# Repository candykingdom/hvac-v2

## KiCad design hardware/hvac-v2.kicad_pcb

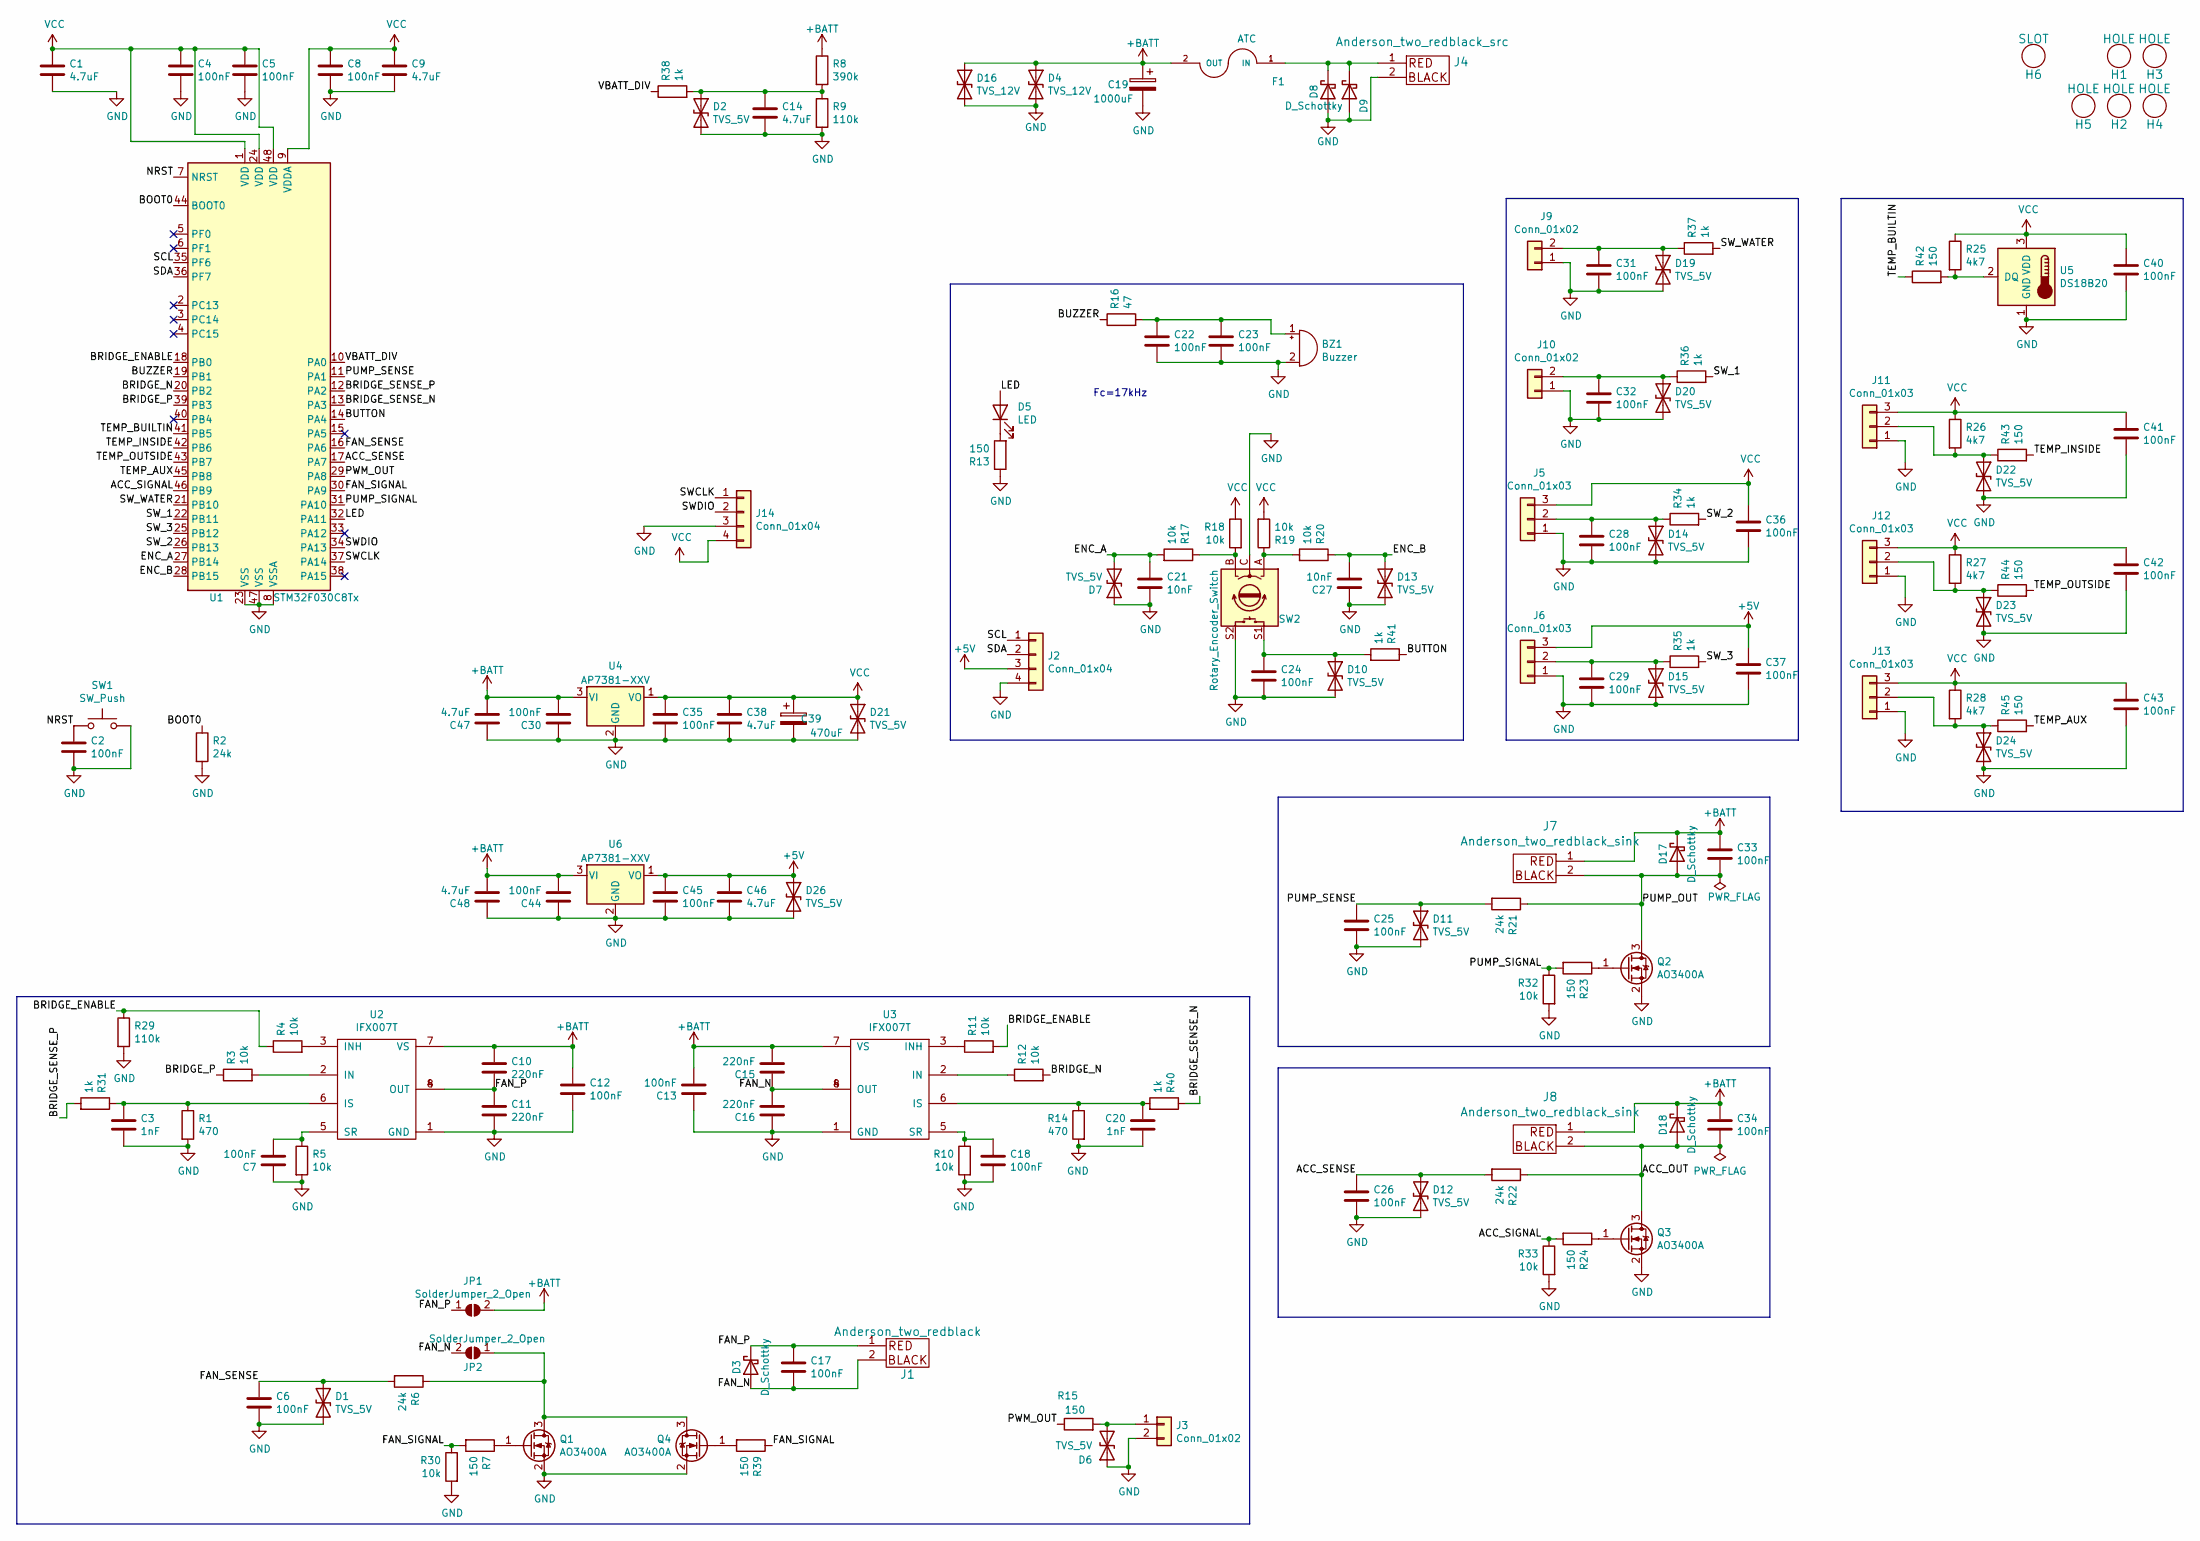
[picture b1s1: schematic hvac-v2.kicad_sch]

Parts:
BZ1: Buzzer; MURATA_PKM13EPYH4000-A0; MPN PKM13EPYH4000-A0
C1, C9, C14, C38, C46, C47, C48: 4.7uF; C_0603_1608Metric; LCSC C19666
C2, C4, C5, C6, C7, C8, C12, C13, C17, C18, C22, C23, C24, C25, C26, C28, C29, C30, C31, C32, C33, C34, C35, C36, C37, C40, C41, C42, C43, C44, C45: 100nF; C_0402_1005Metric; LCSC C307331
C3, C20: 1nF; C_0402_1005Metric; LCSC C1523
C10, C11, C15, C16: 220nF; C_0805_2012Metric; LCSC C5378
C19: 1000uF; CP_Radial_D10.0mm_P5.00mm; MPN 25PK1000MEFC10X16
C21, C27: 10nF; C_0402_1005Metric; LCSC C15195
C39: 470uF; CP_Radial_D10.0mm_P5.00mm; MPN 25PK1000MEFC10X16
D1, D2, D6, D7, D10, D11, D12, D13, D14, D15, D19, D20, D21, D22, D23, D24, D26: TVS_5V; D_SOD-323; LCSC C182013
D3, D8, D9, D17, D18: D_Schottky; D_DO-201AD_P12.70mm_Horizontal; MPN SB10150TA
D4, D16: TVS_12V; D_SMB_Handsoldering; MPN SMBJ16CA
D5: LED; LED_0805_2012Metric; LCSC C84256
F1: ATC; FUSE_3550-2; MPN 3550-2
H1, H2, H3, H4, H5: HOLE; HOLE_M4
H6: SLOT; SLOT_W2mm_H8mm
J1: Anderson_two_redblack; Anderson_1336G1_right_angle_bottom_two
J2, J14: Conn_01x04; PinHeader_1x04_P2.54mm_Horizontal
J3, J9, J10: Conn_01x02; PinHeader_1x02_P2.54mm_Horizontal
J4: Anderson_two_redblack_src; Anderson_1336G1_right_angle_bottom_two
J5, J6, J11, J12, J13: Conn_01x03; PinHeader_1x03_P2.54mm_Horizontal
J7, J8: Anderson_two_redblack_sink; Anderson_1336G1_right_angle_bottom_two
JP1, JP2: SolderJumper_2_Open; SolderJumper-2_P1.3mm_Open_TrianglePad1.0x1.5mm
Q1, Q2, Q3, Q4: AO3400A; SOT-23; LCSC C20917
R1, R14: 470; R_0603_1608Metric; LCSC C23179
R2, R6, R21, R22: 24k; R_0603_1608Metric; LCSC C23352
R3, R4, R5, R10, R11, R12, R17, R18, R19, R20, R30, R32, R33: 10k; R_0603_1608Metric; LCSC C25804
R7, R13, R15, R23, R24, R39, R42, R43, R44, R45: 150; R_0603_1608Metric; LCSC C22808
R8: 390k; R_0603_1608Metric; LCSC C23150
R9, R29: 110k; R_0603_1608Metric; LCSC C25805
R16: 47; R_0603_1608Metric; LCSC C23182
R25, R26, R27, R28: 4k7; R_0603_1608Metric; LCSC C23162
R31, R40, R41: 1k; R_0603_1608Metric; LCSC C11702
R34, R35, R36, R37, R38: 1k; R_0603_1608Metric; LCSC C22808
SW1: SW_Push; SW_TACTILE_5.1MM_TS-1187A-C-D-B; LCSC C318884
SW2: Rotary_Encoder_Switch; BOURNS_PEC12R-4xxxF-Sxxxx; MPN PEC12R-4230F-S0024
U1: STM32F030C8Tx; LQFP-48_7x7mm_P0.5mm; LCSC C23922
U2, U3: IFX007T; TO-263-7_TabPin8; MPN IFX007T
U4: AP7381-XXV; TO-92L_Inline_Wide; MPN AP7381-33V
U5: DS18B20; TO-92_Inline; MPN DS18B20
U6: AP7381-XXV; TO-92L_Inline_Wide; MPN AP7381-50V

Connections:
+5V: C37.1, C45.1, C46.1, D26.1 (A1), J2.3, J6.3, U6.1 (VO)
+BATT: C10.1, C12.1, C13.2, C15.2, C19.1, C30.2, C33.1, C34.1, C44.2, C47.2, C48.2, D4.1 (A1), D16.1 (A1), D17.1 (K), D18.1 (K), F1.2 (OUT), J7.1, J8.1, JP1.2 (B), R8.1, U2.7 (VS), U3.7 (VS), U4.3 (VI), U6.3 (VI)
/ACC_OUT: C34.2, D18.2 (A), J8.2, Q3.3 (D), R22.1
/ACC_SENSE: C26.1, D12.1 (A1), R22.2, U1.17 (PA7)
/ACC_SIGNAL: R24.2, R33.1, U1.46 (PB9)
/BOOT0: R2.1, U1.44 (BOOT0)
/BRIDGE_ENABLE: R4.1, R11.2, R29.1, U1.18 (PB0)
/BRIDGE_N: R12.2, U1.20 (PB2)
/BRIDGE_P: R3.1, U1.39 (PB3)
/BRIDGE_SENSE_N: R40.1, U1.13 (PA3)
/BRIDGE_SENSE_P: R31.2, U1.12 (PA2)
/BUTTON: R41.1, U1.14 (PA4)
/BUZZER: R16.1, U1.19 (PB1)
/ENC_A: C21.1, D7.2 (A2), R17.2, U1.27 (PB14)
/ENC_B: C27.2, D13.1 (A1), R20.1, U1.28 (PB15)
/FAN_N: C15.1, C16.2, C17.2, D3.2 (A), J1.2, JP2.2 (B), U3.4 (OUT), U3.8 (OUT)
/FAN_P: C10.2, C11.1, C17.1, D3.1 (K), J1.1, JP1.1 (A), U2.4 (OUT), U2.8 (OUT)
/FAN_SENSE: C6.1, D1.1 (A1), R6.2, U1.16 (PA6)
/FAN_SIGNAL: R7.2, R30.1, R39.1, U1.30 (PA9)
/LED: D5.2 (A), U1.32 (PA11)
/NRST: C2.1, SW1.1, U1.7 (NRST)
/PUMP_OUT: C33.2, D17.2 (A), J7.2, Q2.3 (D), R21.1
/PUMP_SENSE: C25.1, D11.1 (A1), R21.2, U1.11 (PA1)
/PUMP_SIGNAL: R23.2, R32.1, U1.31 (PA10)
/PWM_OUT: R15.1, U1.29 (PA8)
/SCL: J2.1, U1.35 (PF6)
/SDA: J2.2, U1.36 (PF7)
/SWCLK: J14.1, U1.37 (PA14)
/SWDIO: J14.2, U1.34 (PA13)
/SW_1: R36.2, U1.22 (PB11)
/SW_2: R34.2, U1.26 (PB13)
/SW_3: R35.2, U1.25 (PB12)
/SW_WATER: R37.2, U1.21 (PB10)
/TEMP_AUX: R45.2, U1.45 (PB8)
/TEMP_BUILTIN: R42.1, U1.41 (PB5)
/TEMP_INSIDE: R43.2, U1.42 (PB6)
/TEMP_OUTSIDE: R44.2, U1.43 (PB7)
/VBATT_DIV: R38.1, U1.10 (PA0)
GND: BZ1.2 (+), C1.2, C2.2, C3.2, C4.2, C5.2, C6.2, C7.1, C8.2, C9.2, C11.2, C12.2, C13.1, C14.2, C16.1, C18.2, C19.2, C20.2, C21.2, C22.2, C23.2, C24.2, C25.2, C26.2, C27.1, C28.2, C29.2, C30.1, C31.2, C32.2, C35.2, C36.2, C37.2, C38.2, C39.2, C40.2, C41.2, C42.2, C43.2, C44.1, C45.2, C46.2, C47.1, C48.1, D1.2 (A2), D2.2 (A2), D4.2 (A2), D6.1 (A1), D7.1 (A1), D8.2 (A), D9.2 (A), D10.2 (A2), D11.2 (A2), D12.2 (A2), D13.2 (A2), D14.2 (A2), D15.2 (A2), D16.2 (A2), D19.2 (A2), D20.2 (A2), D21.2 (A2), D22.2 (A2), D23.2 (A2), D24.2 (A2), D26.2 (A2), J2.4, J3.2, J4.2, J5.1, J6.1, J9.1, J10.1, J11.1, J12.1, J13.1, J14.3, Q1.2 (S), Q2.2 (S), Q3.2 (S), Q4.2 (S), R1.2, R2.2, R5.2, R9.2, R10.2, R13.1, R14.2, R29.2, R30.2, R32.2, R33.2, SW1.2, SW2.C, SW2.S2, U1.8 (VSSA), U1.23 (VSS), U1.47 (VSS), U2.1 (GND), U3.1 (GND), U4.2 (GND), U5.1 (GND), U6.2 (GND)
unnamed: BZ1.1 (-), C22.1, C23.1, R16.2
unnamed: C3.1, R1.1, R31.1, U2.6 (IS)
unnamed: C7.2, R5.1, U2.5 (SR)
unnamed: C14.1, D2.1 (A1), R8.2, R9.1, R38.2
unnamed: C18.1, R10.1, U3.5 (SR)
unnamed: C20.1, R14.1, R40.2, U3.6 (IS)
unnamed: C24.1, D10.1 (A1), R41.2, SW2.S1
unnamed: C28.1, D14.1 (A1), J5.2, R34.1
unnamed: C29.1, D15.1 (A1), J6.2, R35.1
unnamed: C31.1, D19.1 (A1), J9.2, R37.1
unnamed: C32.1, D20.1 (A1), J10.2, R36.1
unnamed: D5.1 (K), R13.2
unnamed: D6.2 (A2), J3.1, R15.2
unnamed: D8.1 (K), D9.1 (K), F1.1 (IN), J4.1
unnamed: D22.1 (A1), J11.2, R26.2, R43.1
unnamed: D23.1 (A1), J12.2, R27.2, R44.1
unnamed: D24.1 (A1), J13.2, R28.2, R45.1
unnamed: JP2.1 (A), Q1.3 (D), Q4.3 (D), R6.1
unnamed: Q1.1 (G), R7.1
unnamed: Q2.1 (G), R23.1
unnamed: Q3.1 (G), R24.1
unnamed: Q4.1 (G), R39.2
unnamed: R3.2, U2.2 (IN)
unnamed: R4.2, U2.3 (INH)
unnamed: R11.1, U3.3 (INH)
unnamed: R12.1, U3.2 (IN)
unnamed: R17.1, R18.2, SW2.B
unnamed: R19.1, R20.2, SW2.A
unnamed: R25.2, R42.2, U5.2 (DQ)
VCC: C1.1, C4.1, C5.1, C8.1, C9.1, C35.1, C36.1, C38.1, C39.1, C40.1, C41.1, C42.1, C43.1, D21.1 (A1), J5.3, J11.3, J12.3, J13.3, J14.4, R18.1, R19.2, R25.1, R26.1, R27.1, R28.1, U1.1 (VDD), U1.9 (VDDA), U1.24 (VDD), U1.48 (VDD), U4.1 (VO), U5.3 (VDD)

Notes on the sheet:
Fc=17kHz

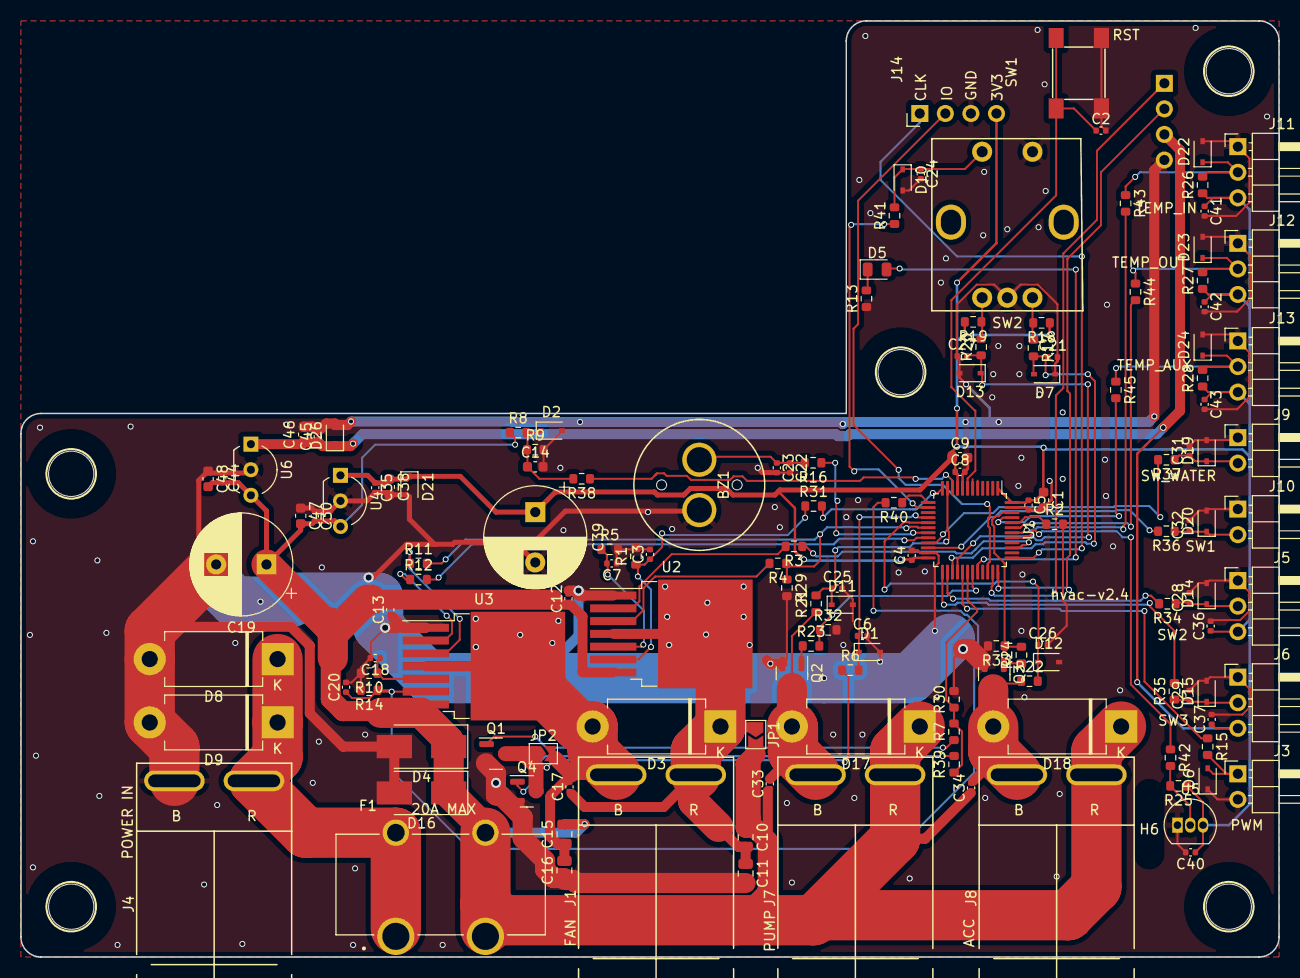
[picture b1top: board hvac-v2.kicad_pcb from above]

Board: 2 copper layers, 125.0 x 93.0 mm, 154 parts (1 on the bottom side), 69 nets.

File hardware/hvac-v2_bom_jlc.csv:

"Comment","Designator","Footprint","LCSC Part #"
"4.7uF","C1,C9,C14,C38,C46,C47,C48","C_0603_1608Metric","C19666"
"100nF","C2,C4,C5,C6,C7,C8,C12,C13,C17,C18,C22,C23,C24,C25,C26,C28,C29,C30,C31,C32,C33,C34,C35,C36,C37,C40,C41,C42,C43,C44,C45","C_0402_1005Metric","C307331"
"1nF","C3,C20","C_0402_1005Metric","C1523"
"220nF","C10,C11,C15,C16","C_0805_2012Metric","C5378"
"10nF","C21,C27","C_0402_1005Metric","C15195"
"TVS_5V","D1,D2,D6,D7,D10,D11,D12,D13,D14,D15,D19,D20,D21,D22,D23,D24,D26","D_SOD-323","C182013"
"LED","D5","LED_0805_2012Metric","C84256"
"AO3400A","Q1,Q2,Q3,Q4","SOT-23","C20917"
"470","R1,R14","R_0603_1608Metric","C23179"
"24k","R2,R6,R21,R22","R_0603_1608Metric","C23352"
"10k","R3,R4,R5,R10,R11,R12,R17,R18,R19,R20,R30,R32,R33","R_0603_1608Metric","C25804"
"150","R7,R13,R15,R23,R24,R39,R42,R43,R44,R45","R_0603_1608Metric","C22808"
"390k","R8","R_0603_1608Metric","C23150"
"110k","R9,R29","R_0603_1608Metric","C25805"
"47","R16","R_0603_1608Metric","C23182"
"4k7","R25,R26,R27,R28","R_0603_1608Metric","C23162"
"1k","R31,R40,R41","R_0603_1608Metric","C11702"
"1k","R34,R35,R36,R37,R38","R_0603_1608Metric","C22808"
"SW_Push","SW1","SW_TACTILE_5.1MM_TS-1187A-C-D-B","C318884"
"STM32F030C8Tx","U1","LQFP-48_7x7mm_P0.5mm","C23922"

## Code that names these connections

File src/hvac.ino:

#include <LiquidCrystal_I2C.h>
#include <STM32TimerInterrupt.h>
#include <STM32_ISR_Timer.h>
#include <Tone.h>
#include <Wire.h>
#include <menu.h>
#include <menuIO/chainStream.h>
#include <menuIO/clickEncoderIn.h>
#include <menuIO/liquidCrystalOutI2C.h>
#include <menuIO/serialIn.h>
#include <menuIO/serialOut.h>
#include <FlashStorage_STM32.h>

#include "arduino-inputs.h"
#include "arduino-outputs.h"
#include "fake-outputs.h"
#include "inputs.h"
#include "outputs.h"
#include "runner.h"

// Pin definitions
constexpr int kBuzzerPin = PB1;
constexpr int kEncAPin = PB14;
constexpr int kEncBPin = PB15;
// TODO: switch to actual encoder button once its connected to the micro
// constexpr int kEncButtonPin = PB11; // v2.3 with hotfix
constexpr int kEncButtonPin = PA4;  // v2.4

constexpr int kFanSensePin = PA6;
constexpr int kPumpSensePin = PA1;
constexpr int kBridgeSenseNPin = PA3;
constexpr int kBridgeSensePPin = PA2;

// Tuning constants
constexpr uint16_t kUpdateTempMs = 1000;
constexpr uint32_t kIdleBacklightOffMs = 30 * 1000;

// State
uint32_t update_display_at = 0;
uint32_t backlight_off_at = 0;

const constexpr int kMaxDepth = 4;

constexpr FanType kFanType = FanType::MOSFET_BANGBANG;
ArduinoInputs inputs;
ArduinoOutputs outputs(kFanType);

RunnerParams runner_params;
Runner runner(runner_params, inputs, outputs);

uint16_t fan_sense = 0;
uint16_t pump_sense = 0;
uint16_t bridge_sense_n = 0;
uint16_t bridge_sense_p = 0;

LiquidCrystal_I2C lcd(/*address=*/0x27, /*columns=*/16, /*rows=*/2);
ClickEncoder clickEncoder(kEncAPin, kEncBPin, kEncButtonPin,
                          /*stepsPerNotch=*/4);
ClickEncoderStream encStream(clickEncoder, 1);

void SaveConfig() {
  EEPROM.put(0, runner_params);
}

// clang-format off
TOGGLE(runner_params.sound_on, sound_on_menu, "Sound:", doNothing, noEvent, wrapStyle
  ,VALUE("On", true, doNothing, noEvent)
  ,VALUE("Off", false, doNothing, noEvent)
);

TOGGLE(runner_params.use_water_switch, water_switch_menu, "WaterSwitch:", doNothing, noEvent, wrapStyle
  ,VALUE("Yes", true, doNothing, noEvent)
  ,VALUE(" No", false, doNothing, noEvent)
);

TOGGLE(runner_params.swamp_direction, swamp_direction_menu, "SwampDir:", doNothing, noEvent, wrapStyle
  ,VALUE("Forw", true, doNothing, noEvent)
  ,VALUE("Back", false, doNothing, noEvent)
);

TOGGLE(runner_params.vent_direction, vent_direction_menu, "VentDir:", doNothing, noEvent, wrapStyle
  ,VALUE("Forw", true, doNothing, noEvent)
  ,VALUE("Back", false, doNothing, noEvent)
);

MENU(config_menu,"Config",doNothing,noEvent,wrapStyle
  ,FIELD(runner_params.temp_deadband, "Temp Band", "F", 0, 20, 1, 0.1, doNothing, noEvent, wrapStyle)
  ,SUBMENU(water_switch_menu)
  ,FIELD(runner_params.pump_period, "Pump Cycle", "s", 0, 999, 60, 5, doNothing, noEvent, wrapStyle)
  ,FIELD(runner_params.pump_duty, "Pump Duty", "", 0, 255, 25, 1, doNothing, noEvent, wrapStyle)
  ,SUBMENU(swamp_direction_menu)
  ,SUBMENU(vent_direction_menu)
  ,SUBMENU(sound_on_menu)
  ,EXIT("...")
);

MENU(sense_menu,"Sense",doNothing,noEvent,wrapStyle
  ,FIELD(fan_sense, "Fan sense", "", 0, 4096, 0, 0, doNothing, noEvent, wrapStyle)
  ,FIELD(pump_sense, "Pump sense", "", 0, 4096, 0, 0, doNothing, noEvent, wrapStyle)
  ,FIELD(bridge_sense_n, "Bridge P", "", 0, 4096, 0, 0, doNothing, noEvent, wrapStyle)
  ,FIELD(bridge_sense_p, "Bridge N", "", 0, 4096, 0, 0, doNothing, noEvent, wrapStyle)
  ,EXIT("...")
);

TOGGLE(runner_params.run_mode, mode_menu, "Mode:", doNothing, noEvent, wrapStyle
  ,VALUE("Auto", RunMode::AUTO, doNothing, noEvent)
  ,VALUE("Swamp", RunMode::SWAMP, doNothing, noEvent)
  ,VALUE("Vent", RunMode::VENT, doNothing, noEvent)
  ,VALUE("Off", RunMode::OFF, doNothing, noEvent)
);

MENU(main_menu,"Main menu",doNothing,noEvent,wrapStyle
  ,SUBMENU(mode_menu)
  ,FIELD(runner_params.set_temp, "Temp", "F", 30, 100, 10, 1, doNothing, noEvent, wrapStyle)
  ,FIELD(runner_params.swamp_fan_speed, "SwampFan", "", 0, 255, 25, 1, doNothing, updateEvent, wrapStyle)
  ,FIELD(runner_params.vent_fan_speed, "VentFan ", "", 0, 255, 25, 1, doNothing, updateEvent, wrapStyle)
  ,FIELD(runner_params.pump_speed, "Pump", "", 0, 255, 25, 1, doNothing, updateEvent, wrapStyle)
  ,FIELD(runner_params.swamp_threshold, "Swamp Thresh", "F", 30, 100, 10, 1, doNothing, noEvent, wrapStyle)
  ,SUBMENU(config_menu)
  ,SUBMENU(sense_menu)
  ,OP("Save", SaveConfig, enterEvent)
  ,EXIT("...")
);

// clang-format on

MENU_INPUTS(in, &encStream);
const Menu::panel panels[] MEMMODE = {{0, 0, 16, 2}};
Menu::navNode *nodes[sizeof(panels) / sizeof(Menu::panel)];
Menu::panelsList pList(panels, nodes, 1);

Menu::idx_t serialTops[kMaxDepth];
Menu::liquidCrystalOut outLCD(lcd, serialTops, pList);

Menu::menuOut *menu_outputs[] MEMMODE = {&outLCD};
Menu::outputsList out(menu_outputs, 1);

// aux objects to control each level of navigation
Menu::navNode nav_cursors[kMaxDepth];
Menu::navRoot nav(main_menu, nav_cursors, kMaxDepth - 1, in, out);

bool in_idle = false;

STM32Timer ITimer(TIM3);
STM32_ISR_Timer ISR_Timer;

void TimerHandler() {
  ISR_Timer.run();
  outputs.Tick();
}

void ServiceEncoder() {
  // outputs.SetLed(true);
  clickEncoder.service();
  // outputs.SetLed(false);
}

result idle(menuOut &o, idleEvent e) {
  switch (e) {
    case idleStart:
      o.clear();
      in_idle = true;
      backlight_off_at = millis() + kIdleBacklightOffMs;
      break;
    case idling:
      break;
    case idleEnd:
      nav.reset();
      in_idle = false;
      backlight_off_at = 0;
      lcd.backlight();
      break;
  }
  return proceed;
}

// In case of non-recoverable error, fast-blink the LED
void FatalError() {
  bool on = true;
  if (runner_params.sound_on) {
    tone(kBuzzerPin, 4000, 100);
  }
  while (true) {
    outputs.SetLed(on);
    on = !on;
    delay(200);
  }
}

void Warning() {
  bool on = true;
  for (int i = 0; i < 4; i++) {
    outputs.SetLed(on);
    if (on && runner_params.sound_on) {
      tone(kBuzzerPin, 4000, 500);
    }
    on = !on;
    delay(500);
  }
}

void setup() {
  // If the flash storage has been written before, load config from it.
  // Note: this seems to return true always, so we double-check using `runner_params.valid`.
  if (EEPROM.isValid()) {
    EEPROM.get(0, runner_params);
  }
  if (runner_params.valid != RunnerParams::kValid) {
    runner_params.SetDefaults();
  }
  
  if (!outputs.Init()) {
    Serial.println("outputs.Init() failed");
    Warning();
  }

  pinMode(kBuzzerPin, OUTPUT);
  pinMode(kEncAPin, INPUT);
  pinMode(kEncBPin, INPUT);
  pinMode(kEncButtonPin, INPUT_PULLUP);

  pinMode(kFanSensePin, INPUT);
  pinMode(kPumpSensePin, INPUT);

  pinMode(kBridgeSenseNPin, INPUT);
  pinMode(kBridgeSensePPin, INPUT);

  if (!inputs.Init()) {
    Serial.println("inputs.Init() failed");
    Warning();
  }
  nav.timeOut = 10;
  nav.idleTask = idle;
  nav.useUpdateEvent = true;

  Wire.setSCL(PF6);
  Wire.setSDA(PF7);
  lcd.init();
  lcd.backlight();

  // 75uS * 256 ~= 50Hz
  if (!ITimer.attachInterruptInterval(75, TimerHandler)) {
    FatalError();
  }
  // Poll the encoder every 1ms
  ISR_Timer.setInterval(1, ServiceEncoder);

  // Make sense display read-only
  sense_menu[0].disable();
  sense_menu[1].disable();
  sense_menu[2].disable();
  sense_menu[3].disable();
}

void loop() {
  if (in_idle && millis() > update_display_at) {
    lcd.home();
    lcd.print("Out ");
    float outside = inputs.GetOutside();
    if (outside <= ArduinoInputs::kNoTemp) {
      lcd.print("NA");
    } else {
      lcd.print(inputs.GetOutside(), /* digits= */ 0);
    }

    lcd.print("   In ");
    float inside = inputs.GetInside();
    if (inside <= ArduinoInputs::kNoTemp) {
      lcd.print("NA   ");
    } else {
      lcd.print(inputs.GetInside(), /* digits= */ 0);
      lcd.print("   ");
    }

    lcd.setCursor(/*col=*/0, /*row=*/1);
    if (runner_params.run_mode == RunMode::OFF) {
      lcd.print("Off");
    } else if ((runner_params.run_mode == RunMode::AUTO ||
                runner_params.run_mode == RunMode::SWAMP) &&
               runner_params.use_water_switch && !inputs.GetWaterSwitch()) {
      lcd.print("No Water!        ");
    } else {
      lcd.print("Fan ");
      uint8_t fan = outputs.GetFan();
      if (fan == 255) {
        lcd.print(" ON");
      } else if (fan == 0) {
        lcd.print("OFF");
      } else {
        lcd.print(fan);
      }

      lcd.print(" Pump ");
      uint8_t pump = outputs.GetPump();
      if (pump == 255) {
        lcd.print(" ON");
      } else if (pump == 0) {
        lcd.print("OFF");
      } else {
        lcd.print(pump);
      }
    }

    update_display_at = millis() + kUpdateTempMs;
  }

  if (backlight_off_at && millis() > backlight_off_at) {
    lcd.noBacklight();
    backlight_off_at = 0;
  }

  runner.Tick();

  fan_sense = analogRead(kFanSensePin);
  pump_sense = analogRead(kPumpSensePin);
  bridge_sense_n = analogRead(kBridgeSenseNPin);
  bridge_sense_p = analogRead(kBridgeSensePPin);

  nav.poll();
}

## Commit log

2018-07-20 Initial commit - first pass at v2.0 schematic
2018-07-20 Added footprints
2018-07-21 Rename to hvac
2018-07-21 Place the parts neessary to be HVAC
2018-07-21 Switch to a potentiometer for mode control
2018-07-21 Associate footprints
2018-07-21 Regenerate netlist
2018-07-21 First pass rough placement
2018-07-21 Route power (GIANT TRACES)
2018-07-21 First pass routing. Still has DRC errors
2018-07-21 DRC fixes
2018-07-21 More DRC fixes
2018-07-21 Move cut line up by a mm
2018-07-21 Add silkscreen version and test/cal
2018-07-22 Place the programming header and diode
2018-07-22 More silkscreens + generate assembly sheet
2018-07-22 Connect programming headers
2018-08-01 Hardware revision 2.1: - Fix SWD connection to power to not connect directly to VCC - Add silk labels for controls
2018-08-18 Add test sketch
2018-08-18 Make FastLED work
2018-08-18 Add basic control
2018-08-18 Add speed control
2018-08-19 Fix temp loop to actually request temperature
2018-08-19 Add power led
2018-08-19 Only request temp in temp loop - fixes broken fan speed button
2018-08-19 make fan speed LED pulse brighter
2022-04-19 Start updating schematic for JLC assembly
2022-04-20 Start adding motor drivers
2022-04-22 Finish updating schematic for JLC assembly
2022-04-22 Start placing components
2022-04-23 Component placement finished
2022-04-23 Start routing
2022-04-23 Update to KiCAD v6 format
2022-04-23 First pass at routing
2022-04-24 Hardware revision v2.2.
    Complete redesign. Has an I2C port for a screen and a rotary encoder
    with a button. Is designed for SMT assembly using JLCPCB.
2022-05-04 Add basic Arduino Menu usage
2022-05-04 Try to add temp display (not refreshing)
2022-05-04 Add idle
2022-05-04 Move PCB to subdir
2022-05-13 Display temps on idle
2022-05-13 Untrack build and KiCAD backup dirs
2022-05-13 Move temps to a class, instead of static methods
2022-05-13 Add CI config to build with PlatformIO
2022-05-13 Fix build
2022-05-13 Add outputs
2022-05-13 Rename Temps to Inputs
2022-05-13 Read temp sensors on Arduino
2022-05-13 Add basic thermostat
2022-05-17 Ignore vscode dir
2022-05-17 Configure PlatformIO for actual processor
2022-05-18 Start hardware revision 2.3: fix LCD I2C
2022-05-18 Add buzzer pin
2022-05-20 Complete hardware v2.3:
    - Fix LCD I2C pins
    - Switch to voltage regulators with higher input voltage range
    - Increase 12v line TVS diodes
2022-06-02 Add fan and pump pins
2022-07-08 Hook up the actual LCD to the menuing system
2022-07-08 Use real inputs
2022-07-08 Start adding handling for invalid temperatures
2022-07-08 Turn off backlight when idle
2022-07-08 Display pump and fan status
2022-07-08 Display current sense
2022-07-08 Fix deps
    Update ClickEncoder to use HTTPS, not SSH, and pin versions.
2022-07-09 Add support for all fan output types
2022-07-09 Add config to enable/disable sound
2022-07-09 Add manual mode
2022-07-09 Add test framework
2022-07-09 Start adding tests.
    This moves thermostat functionality into a wrapper class, and adds a
    test which initializes it.
2022-07-09 Set defaults for runner params
2022-07-10 Add battery voltage to inputs
2022-07-10 Enable asan and ubsan for tests
2022-07-10 Add tests for auto and manual mode.
    Also add a script to generate test coverage using lcov.
2022-07-10 Remove unneeded iostream import
2022-07-10 Fix battery voltage
2022-07-10 Add config for fan direction, and seperate speeds for vent and swamp
2022-07-10 Display no water status on LCD
2022-07-10 Add an off mode
2022-07-10 Migrate manual mode to swamp and vent modes
2022-07-10 Disable outputs in auto when temps invalid
2022-07-10 Add ramp for fan PWM
2022-07-10 Add a temp deadband
2022-07-10 Allow setting the temp deadband
2022-07-11 Add duty cycle for pump
2022-07-13 Start updating schematic for v2.4
2022-07-14 Cleanup pump duty cycle
2022-07-19 Hardware revision 2.4:
    - Actually wire encoder button to processor
    - Increase power trace widths
    - Fix encoder RC circuit cap size
    - Add silk labels on top
    - Add protection resistors to all IO
2022-08-03 Add 3d model for pcb
2022-08-13 Add support for savings settings to EEPROM
2022-08-13 Set defaults for configs from flash storage
2022-08-16 Set the OneWire version
2023-02-09 Migrate to async DS18B20 library
2023-02-09 Fix LCD glitches
2023-02-09 Actually check if temp sensors are connected
2023-06-08 Add MOSFET_BANGBANG mode
